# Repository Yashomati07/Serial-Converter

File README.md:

# Serial Converter – PCB Design (KiCad 9)

This repository contains the design files for a **Serial Converter PCB** created using **KiCad 9**. The board provides a simple and effective solution for converting serial communication levels—ideal for embedded systems, microcontroller interfacing, or general-purpose serial communication debugging.

## Features

- Designed in **KiCad 9**
- Converts **TTL ↔ RS232** (or USB, based on configuration)
- Compact and modular PCB layout
- Includes schematics, PCB layout, and ready-to-manufacture Gerber files
- Open-source hardware for learning and development

## Repository Contents

- `*.kicad_pcb` – PCB layout file
- `*.sch` – Schematic diagram (See: [Serial_Converter_Schematic.pdf](./Serial_Converter_Schematic.pdf))
- `*.bom` – Bill of Materials
- `*.gerber/` – Production-ready Gerber files
- `README.md` – Project overview and documentation

## Schematic Preview

*For a detailed view, open the PDF version directly.*

## Tools Required

- **KiCad 9** (or compatible newer versions)
- A PCB fabrication service (e.g., JLCPCB, OSH Park)
- Basic soldering tools and components (listed in BOM)

## Usage

Use this board as a bridge for serial communication between TTL logic devices (like Arduinos, ESP32, STM32, etc.) and RS232 or USB-based interfaces. Modify the schematic to fit your voltage or connector requirements.

## License

This project is licensed under the **MIT License**.
---

Built with passion and precision using **KiCad 9**.

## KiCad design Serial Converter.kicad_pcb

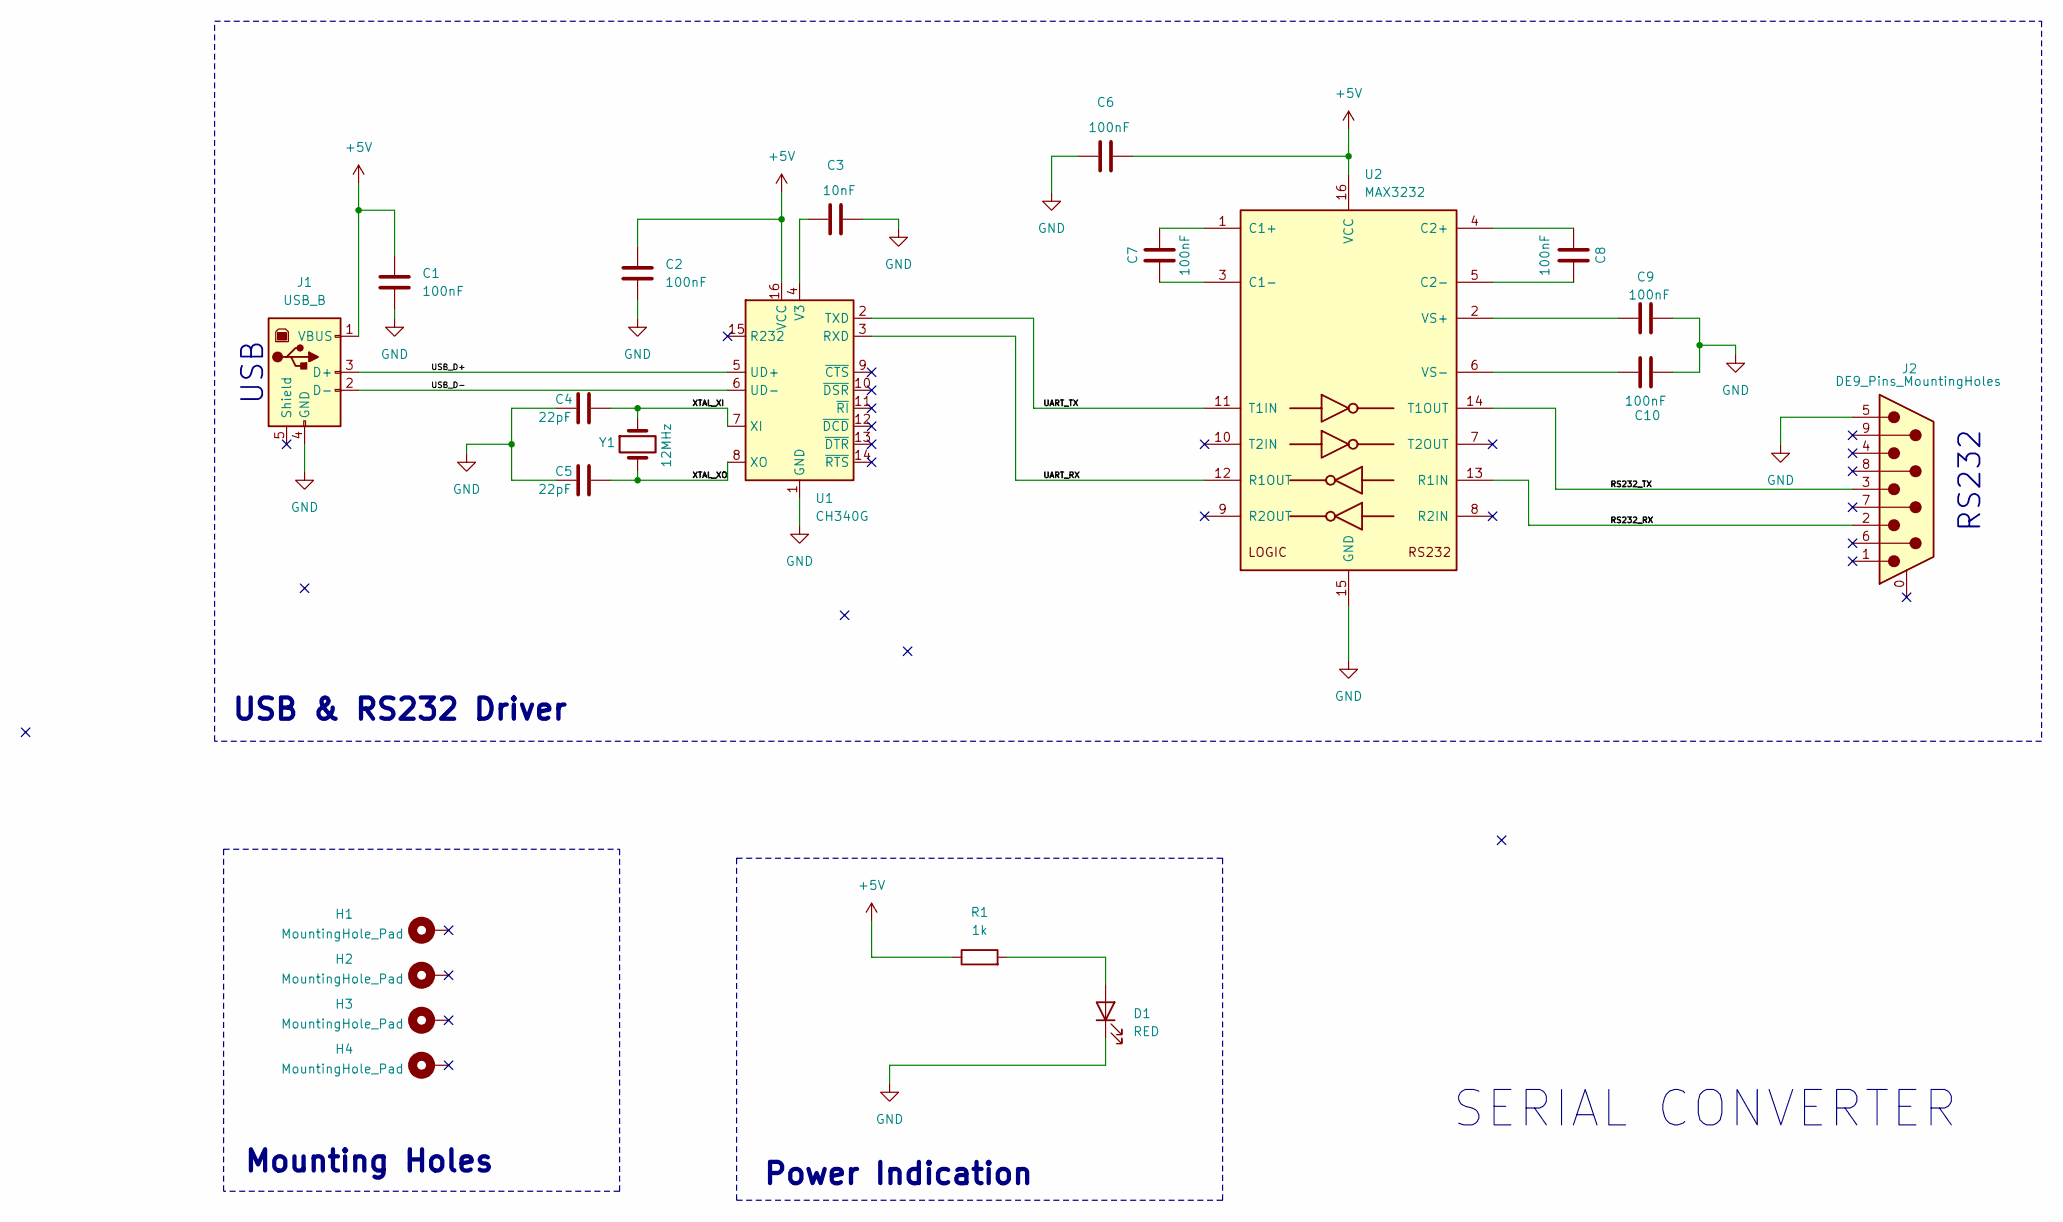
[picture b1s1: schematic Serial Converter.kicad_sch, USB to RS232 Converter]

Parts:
C1, C2, C6, C7, C8, C9, C10: 100nF; C_0805_2012Metric
C3: 10nF; C_0805_2012Metric
C4, C5: 22pF; C_0805_2012Metric
D1: RED; LED_0805_2012Metric
H1, H2, H3, H4: MountingHole_Pad; MountingHole_3.2mm_M3_Pad_Via
J1: USB_B; USB_B_Lumberg_2411_02_Horizontal
J2: DE9_Pins_MountingHoles; DSUB-9_Socket_Horizontal_P2.77x2.84mm_EdgePinOffset4.94mm_H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
R1: 1k; R_0805_2012Metric
U1: CH340G; SOIC-16_3.9x9.9mm_P1.27mm
U2: MAX3232; SOIC-16_3.9x9.9mm_P1.27mm
Y1: 12MHz; Crystal_SMD_HC49-SD

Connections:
+5V: C1.1, C2.1, C6.2, J1.1 (VBUS), R1.1, U1.16 (VCC), U2.16 (VCC)
/RS232_RX: J2.2, U2.13 (R1IN)
/RS232_TX: J2.3, U2.14 (T1OUT)
/UART_RX: U1.3 (RXD), U2.12 (R1OUT)
/UART_TX: U1.2 (TXD), U2.11 (T1IN)
/USB_D+: J1.3 (D+), U1.5 (UD+)
/USB_D-: J1.2 (D-), U1.6 (UD-)
/XTAL_XI: C4.2, U1.7 (XI), Y1.1
/XTAL_XO: C5.2, U1.8 (XO), Y1.2
GND: C1.2, C2.2, C3.2, C4.1, C5.1, C6.1, C9.1, C10.1, D1.1 (K), J1.4 (GND), J2.5, U1.1 (GND), U2.15 (GND)
unnamed: D1.2 (A), R1.2
unnamed: C3.1, U1.4 (V3)
unnamed: C7.2, U2.1 (C1+)
unnamed: C7.1, U2.3 (C1-)
unnamed: C8.2, U2.4 (C2+)
unnamed: C8.1, U2.5 (C2-)
unnamed: C9.2, U2.2 (VS+)
unnamed: C10.2, U2.6 (VS-)

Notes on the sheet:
Power Indication
SERIAL CONVERTER
Mounting Holes
RS232
USB
USB & RS232 Driver

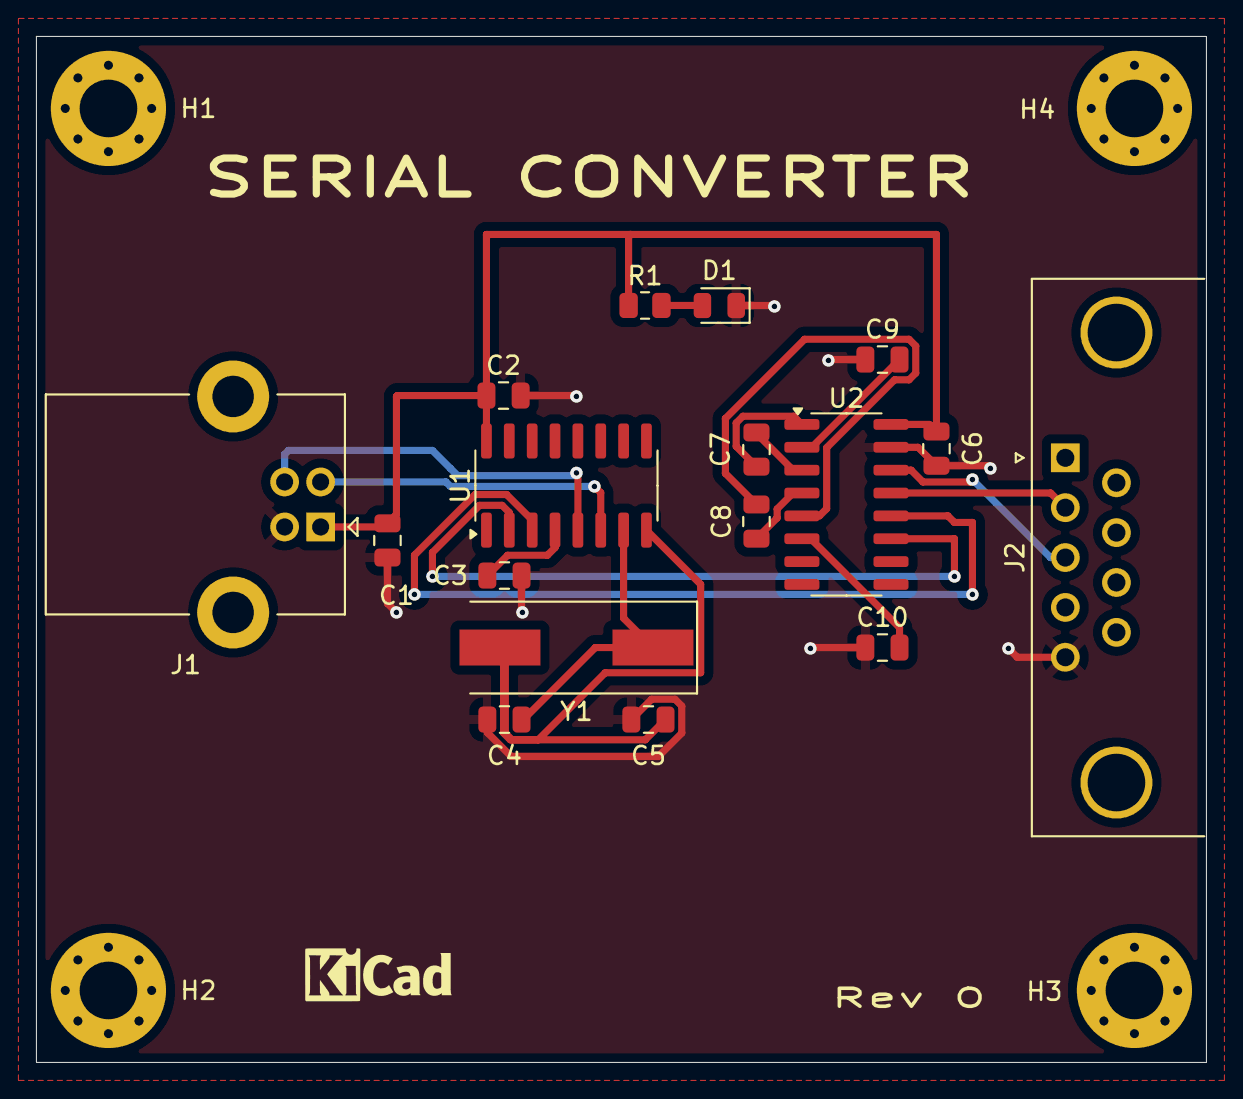
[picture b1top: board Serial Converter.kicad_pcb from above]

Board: 2 copper layers, 65.0 x 57.0 mm, 21 parts (0 on the bottom side), 18 nets.

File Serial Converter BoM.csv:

"Reference","Value","Footprint","Datasheet","Qty","DNP","Exclude from BOM","Exclude from Board"
"C1,C2,C6,C7,C8,C9,C10","100nF","Capacitor_SMD:C_0805_2012Metric","~","7","","",""
"C3","10nF","Capacitor_SMD:C_0805_2012Metric","~","1","","",""
"C4,C5","22pF","Capacitor_SMD:C_0805_2012Metric","~","2","","",""
"D1","RED","LED_SMD:LED_0805_2012Metric","~","1","","",""
"H1,H2,H3,H4","MountingHole_Pad","MountingHole:MountingHole_3.2mm_M3_Pad_Via","~","4","","Excluded from BOM",""
"J1","USB_B","Connector_USB:USB_B_Lumberg_2411_02_Horizontal","~","1","","",""
"J2","DE9_Pins_MountingHoles","Connector_Dsub:DSUB-9_Socket_Horizontal_P2.77x2.84mm_EdgePinOffset4.94mm_Housed_MountingHolesOffset4.94mm","~","1","","",""
"R1","1k","Resistor_SMD:R_0805_2012Metric","~","1","","",""
"U1","CH340G","Package_SO:SOIC-16_3.9x9.9mm_P1.27mm","http://www.datasheet5.com/pdf-local-2195953","1","","",""
"U2","MAX3232","Package_SO:SOIC-16_3.9x9.9mm_P1.27mm","https://datasheets.maximintegrated.com/en/ds/MAX3222-MAX3241.pdf","1","","",""
"Y1","12MHz","Crystal:Crystal_SMD_HC49-SD","~","1","","",""
